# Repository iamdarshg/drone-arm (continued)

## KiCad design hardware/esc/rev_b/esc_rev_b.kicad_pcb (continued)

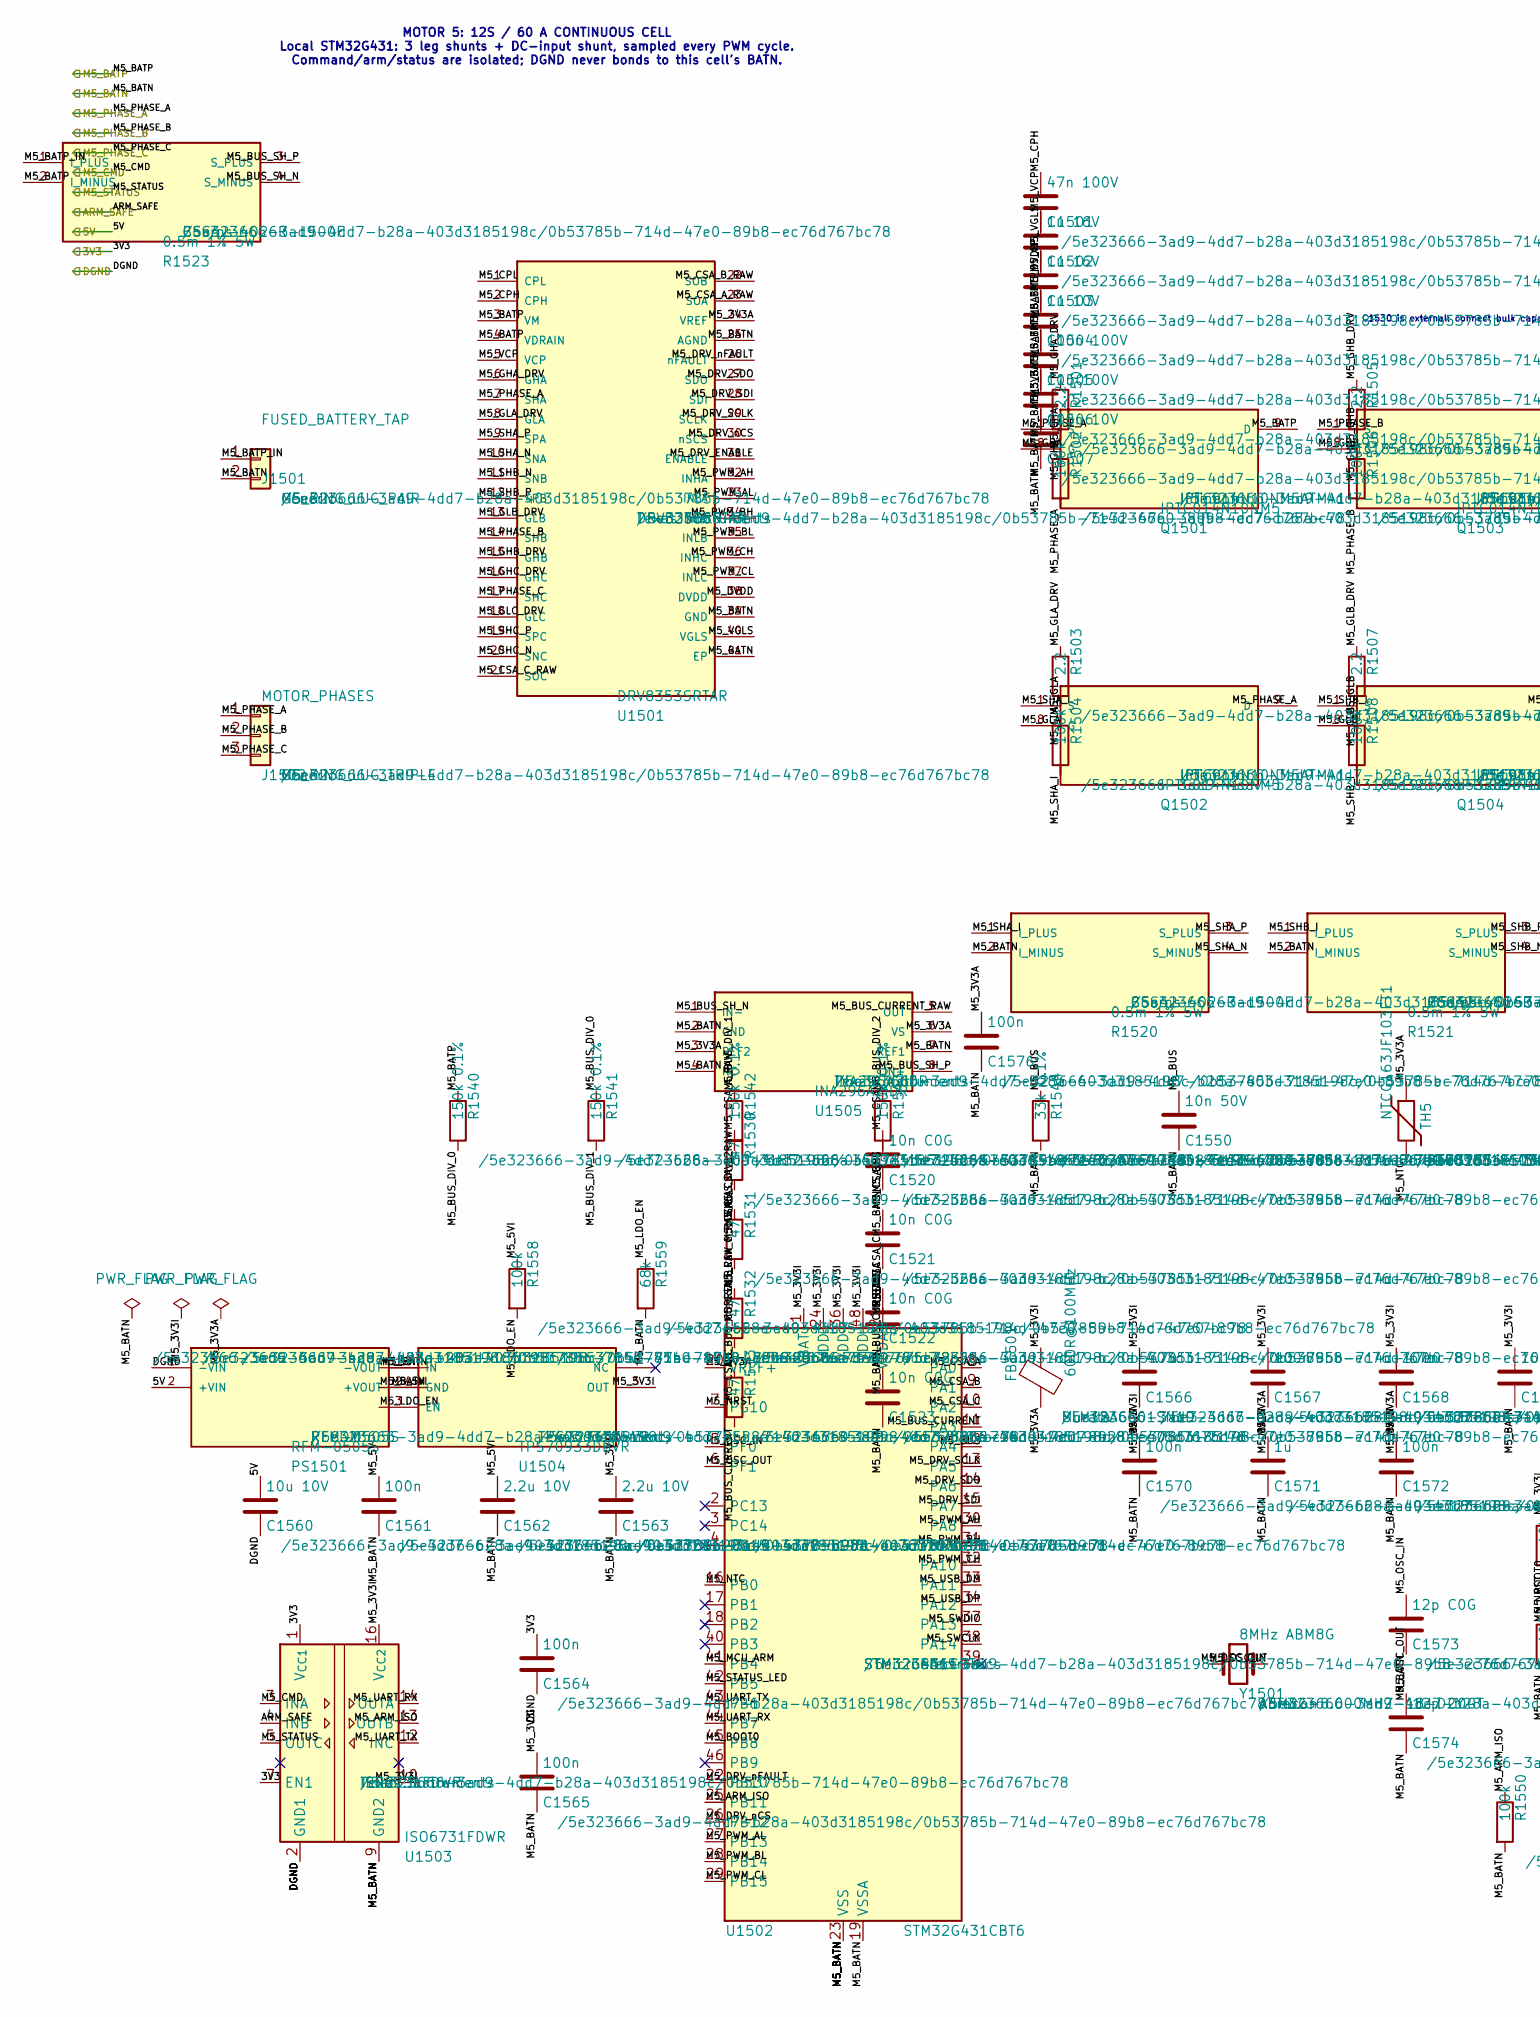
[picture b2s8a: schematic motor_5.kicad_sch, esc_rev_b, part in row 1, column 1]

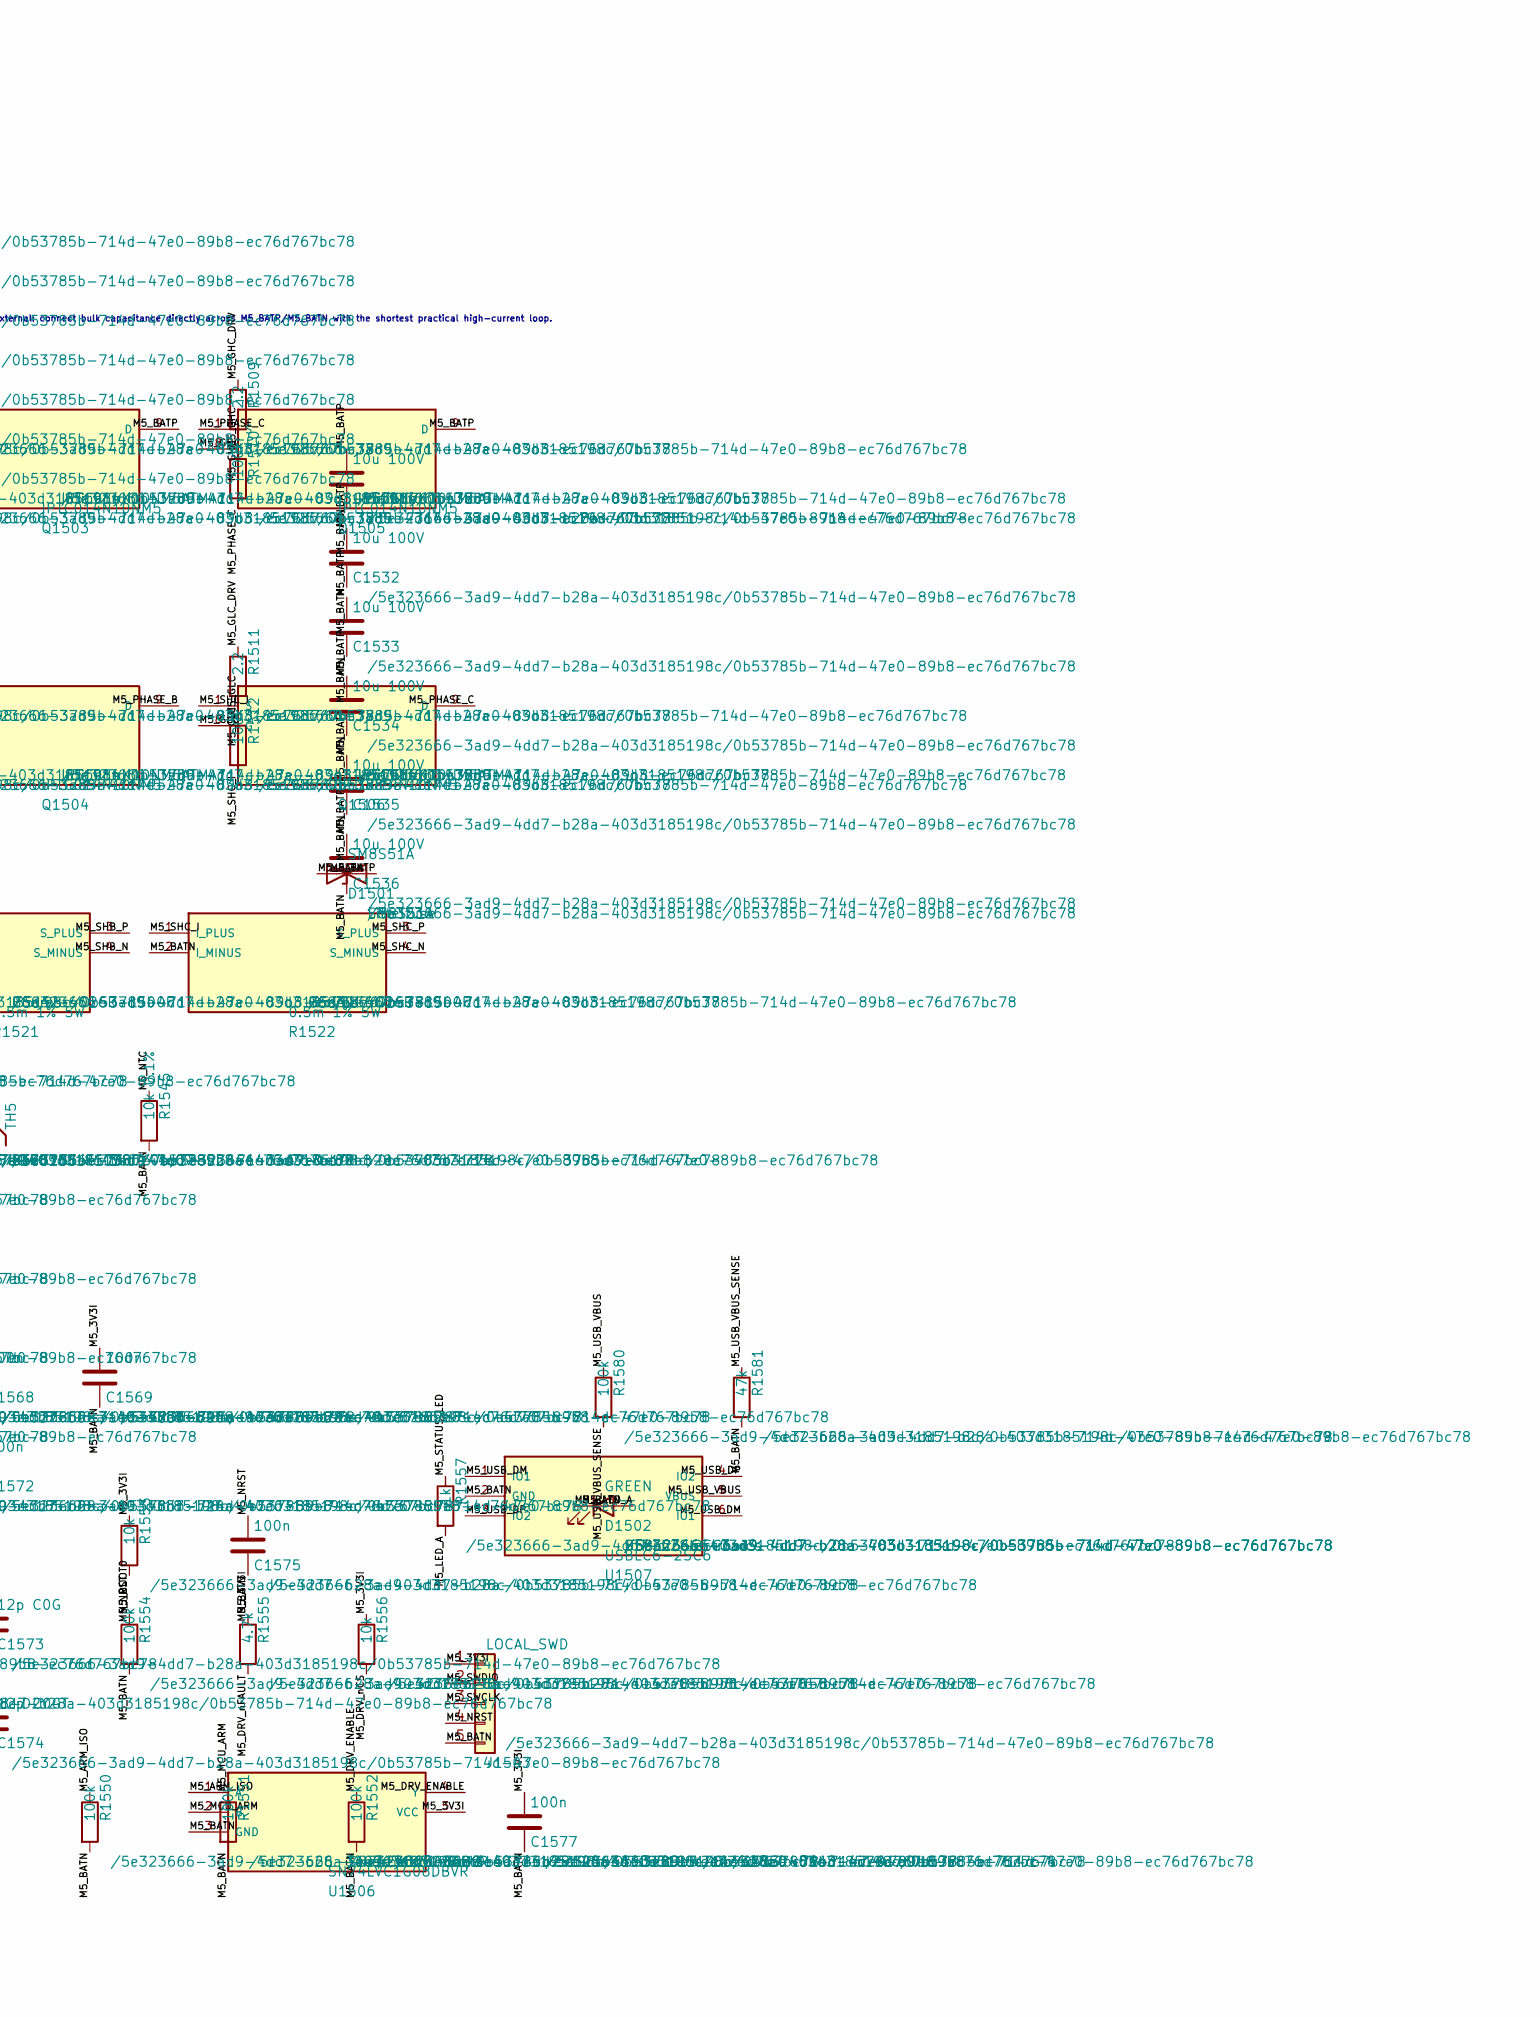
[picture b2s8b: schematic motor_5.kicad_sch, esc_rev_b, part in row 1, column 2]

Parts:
C1501: 47n 100V; C_0603_1608Metric
C1502, C1503: 1u 16V; C_0603_1608Metric
C1504: 1u 10V; C_0603_1608Metric
C1505: 100n 100V; C_0603_1608Metric
C1506, C1531, C1532, C1533, C1534, C1535, C1536: 10u 100V; C_1210_3225Metric
C1507: 100n 10V; C_0603_1608Metric
C1520, C1521, C1522, C1523: 10n C0G; C_0603_1608Metric
C1550: 10n 50V; C_0603_1608Metric
C1560: 10u 10V; C_0805_2012Metric
C1561, C1564, C1565, C1575, C1576, C1577: 100n; C_0603_1608Metric
C1562, C1563: 2.2u 10V; C_0603_1608Metric
C1566: 4.7u; C_0603_1608Metric
C1567, C1568, C1569, C1570, C1572: 100n; C_0402_1005Metric
C1571: 1u; C_0603_1608Metric
C1573, C1574: 12p C0G; C_0402_1005Metric
D1501: SM8S51A; DO-218AB_SM8S; MPN SM8S51A
D1502: GREEN; LED_0603_1608Metric
FB1501: 600R@100MHz; L_0603_1608Metric; MPN BLM18AG601SN1D
J1501: FUSED_BATTERY_TAP; POWER_LUG_M5_2P_P20; MPN M5_RING_LUG_PAIR
J1502: MOTOR_PHASES; POWER_LUG_M5_3P_P20; MPN M5_RING_LUG_TRIPLE
J1503: LOCAL_SWD; PinHeader_1x05_P1.27mm_Vertical
PS1501: RFM-0505S; RFM_SIP4_11.5x6_P2.54; MPN RFM-0505S
Q1501, Q1502, Q1503, Q1504, Q1505, Q1506: IPTC014N10NM5; PG-HDSOP-16_TOLT_IPTC; MPN IPTC014N10NM5ATMA1
R1501, R1503, R1505, R1507, R1509, R1511: 2.2; R_0603_1608Metric
R1502, R1504, R1506, R1508, R1510, R1512, R1550, R1551, R1552, R1554, R1558, R1580: 100k; R_0603_1608Metric
R1520, R1521, R1522, R1523: 0.5m 1% 5W; CSS4J-4026_Kelvin; MPN CSS4J-4026R-L500F
R1530, R1531, R1532, R1533: 47; R_0603_1608Metric
R1540, R1541, R1542, R1543: 150k 0.1%; R_1206_3216Metric
R1544: 33k 0.1%; R_0603_1608Metric
R1545: 10k 0.1%; R_0603_1608Metric
R1553, R1556: 10k; R_0603_1608Metric
R1555: 4.7k; R_0603_1608Metric
R1557: 1k; R_0603_1608Metric
R1559: 68k; R_0603_1608Metric
R1581: 47k; R_0603_1608Metric
TH5: NTCG163JF103FT1; R_0603_1608Metric; MPN NTCG163JF103FT1
U1501: DRV8353SRTAR; WQFN-40-EP_6x6_P0.5; MPN DRV8353SRTAR
U1502: STM32G431CBT6; LQFP-48_7x7mm_P0.5mm; MPN STM32G431CBT6
U1503: ISO6731FDWR; SOIC-16W_7.5x10.3mm_P1.27mm; MPN ISO6731FDWR
U1504: TPS70933DBVR; SOT-23-5; MPN TPS70933DBVR
U1505: INA296A2IDR; SOIC-8_3.9x4.9mm_P1.27mm; MPN INA296A2IDR
U1506: SN74LVC1G08DBVR; SOT-23-5; MPN SN74LVC1G08DBVR
U1507: USBLC6-2SC6; SOT-23-6; MPN USBLC6-2SC6
Y1501: 8MHz ABM8G; Crystal_SMD_3225-4Pin_3.2x2.5mm; MPN ABM8G-8.000MHZ-18-D2Y-T

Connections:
/3V3: C1564.1, U1503.1 (V_{CC1}), U1503.7 (EN1); also elsewhere on the board
/5V: C1560.1, PS1501.2 (+VIN); also elsewhere on the board
/ARM_SAFE: U1503.4 (INB); also elsewhere on the board
/DGND: C1560.2, C1564.2, PS1501.1 (-VIN), U1503.2 (GND1), U1503.8 (GND1); also elsewhere on the board
/M5_BATN: C1503.2, C1504.2, C1505.2, C1506.2, C1507.2, C1520.2, C1521.2, C1522.2, C1523.2, C1531.2, C1532.2, C1533.2, C1534.2, C1535.2, C1536.2, C1550.2, C1561.2, C1562.2, C1563.2, C1565.2, C1566.2, C1567.2, C1568.2, C1569.2, C1570.2, C1571.2, C1572.2, C1573.2, C1574.2, C1575.2, C1576.2, C1577.2, D1501.1 (A1), D1502.1 (K), J1501.2, J1503.5, PS1501.3 (-VOUT), R1520.2 (I_MINUS), R1521.2 (I_MINUS), R1522.2 (I_MINUS), R1544.2, R1545.2, R1550.2, R1551.2, R1552.2, R1554.2, R1559.2, R1581.2, U1501.25 (AGND), U1501.39 (GND), U1501.41 (EP), U1502.19 (VSSA), U1502.23 (VSS), U1502.35 (VSS), U1502.47 (VSS), U1503.9 (GND2), U1503.15 (GND2), U1504.2 (GND), U1505.2 (GND), U1505.4 (NC), U1505.7 (REF1), U1506.3 (GND), U1507.2 (GND); also elsewhere on the board
/M5_BATP: C1502.2, C1505.1, C1506.1, C1531.1, C1532.1, C1533.1, C1534.1, C1535.1, C1536.1, D1501.2 (A2), Q1501.9 (D), Q1503.9 (D), Q1505.9 (D), R1523.2 (I_MINUS), R1540.1, U1501.3 (VM), U1501.4 (VDRAIN); also elsewhere on the board
/M5_CMD: U1503.3 (INA); also elsewhere on the board
/M5_PHASE_A: J1502.1, Q1501.1 (S), Q1502.9 (D), R1502.2, U1501.7 (SHA)
/M5_PHASE_B: J1502.2, Q1503.1 (S), Q1504.9 (D), R1506.2, U1501.14 (SHB)
/M5_PHASE_C: J1502.3, Q1505.1 (S), Q1506.9 (D), R1510.2, U1501.17 (SHC)
/M5_STATUS: U1503.5 (OUTC); also elsewhere on the board
/Motor 5 power cell/M5_3V3A: C1507.1, C1571.1, C1572.1, C1576.1, FB1501.2, TH5.1, U1501.24 (VREF), U1502.20 (VREF+), U1502.21 (VDDA), U1505.3 (REF2), U1505.6 (VS)
/Motor 5 power cell/M5_3V3I: C1563.1, C1565.1, C1566.1, C1567.1, C1568.1, C1569.1, C1570.1, C1577.1, FB1501.1, J1503.1, R1553.1, R1555.1, R1556.1, U1502.1 (VBAT), U1502.24 (VDD), U1502.36 (VDD), U1502.48 (VDD), U1503.10 (EN2), U1503.16 (V_{CC2}), U1504.5 (OUT), U1506.5 (VCC)
/Motor 5 power cell/M5_5VI: C1561.1, C1562.1, PS1501.4 (+VOUT), R1558.1, U1504.1 (IN)
/Motor 5 power cell/M5_ARM_ISO: R1550.1, U1502.25 (PB11), U1503.13 (OUTB), U1506.1 (A)
/Motor 5 power cell/M5_BATP_IN: J1501.1, R1523.1 (I_PLUS)
/Motor 5 power cell/M5_BOOT0: R1554.1, U1502.45 (PB8)
/Motor 5 power cell/M5_BUS: C1550.1, R1543.2, R1544.1, U1502.12 (PA4)
/Motor 5 power cell/M5_BUS_CURRENT: C1523.1, R1533.2, U1502.11 (PA3)
/Motor 5 power cell/M5_BUS_CURRENT_RAW: R1533.1, U1505.5 (OUT)
/Motor 5 power cell/M5_BUS_DIV_0: R1540.2, R1541.1
/Motor 5 power cell/M5_BUS_DIV_1: R1541.2, R1542.1
/Motor 5 power cell/M5_BUS_DIV_2: R1542.2, R1543.1
/Motor 5 power cell/M5_BUS_SH_N: R1523.4 (S_MINUS), U1505.1 (IN-)
/Motor 5 power cell/M5_BUS_SH_P: R1523.3 (S_PLUS), U1505.8 (IN+)
/Motor 5 power cell/M5_CPH: C1501.1, U1501.2 (CPH)
/Motor 5 power cell/M5_CPL: C1501.2, U1501.1 (CPL)
/Motor 5 power cell/M5_CSA_A: C1520.1, R1530.2, U1502.8 (PA0)
/Motor 5 power cell/M5_CSA_A_RAW: R1530.1, U1501.23 (SOA)
/Motor 5 power cell/M5_CSA_B: C1521.1, R1531.2, U1502.9 (PA1)
/Motor 5 power cell/M5_CSA_B_RAW: R1531.1, U1501.22 (SOB)
/Motor 5 power cell/M5_CSA_C: C1522.1, R1532.2, U1502.10 (PA2)
/Motor 5 power cell/M5_CSA_C_RAW: R1532.1, U1501.21 (SOC)
/Motor 5 power cell/M5_DRV_ENABLE: R1552.1, U1501.31 (ENABLE), U1506.4 (Y)
/Motor 5 power cell/M5_DRV_SCLK: U1501.29 (SCLK), U1502.13 (PA5)
/Motor 5 power cell/M5_DRV_SDI: U1501.28 (SDI), U1502.15 (PA7)
/Motor 5 power cell/M5_DRV_SDO: U1501.27 (SDO), U1502.14 (PA6)
/Motor 5 power cell/M5_DRV_nCS: R1556.2, U1501.30 (nSCS), U1502.26 (PB12)
/Motor 5 power cell/M5_DRV_nFAULT: R1555.2, U1501.26 (nFAULT), U1502.22 (PB10)
/Motor 5 power cell/M5_DVDD: C1504.1, U1501.38 (DVDD)
/Motor 5 power cell/M5_GHA: Q1501.8 (G), R1501.2, R1502.1
/Motor 5 power cell/M5_GHA_DRV: R1501.1, U1501.6 (GHA)
/Motor 5 power cell/M5_GHB: Q1503.8 (G), R1505.2, R1506.1
/Motor 5 power cell/M5_GHB_DRV: R1505.1, U1501.15 (GHB)
/Motor 5 power cell/M5_GHC: Q1505.8 (G), R1509.2, R1510.1
/Motor 5 power cell/M5_GHC_DRV: R1509.1, U1501.16 (GHC)
/Motor 5 power cell/M5_GLA: Q1502.8 (G), R1503.2, R1504.1
/Motor 5 power cell/M5_GLA_DRV: R1503.1, U1501.8 (GLA)
/Motor 5 power cell/M5_GLB: Q1504.8 (G), R1507.2, R1508.1
/Motor 5 power cell/M5_GLB_DRV: R1507.1, U1501.13 (GLB)
/Motor 5 power cell/M5_GLC: Q1506.8 (G), R1511.2, R1512.1
/Motor 5 power cell/M5_GLC_DRV: R1511.1, U1501.18 (GLC)
/Motor 5 power cell/M5_LDO_EN: R1558.2, R1559.1, U1504.3 (EN)
/Motor 5 power cell/M5_LED_A: D1502.2 (A), R1557.2
/Motor 5 power cell/M5_MCU_ARM: R1551.1, U1502.41 (PB4), U1506.2 (B)
/Motor 5 power cell/M5_NRST: C1575.1, J1503.4, R1553.2, U1502.7 (PG10)
/Motor 5 power cell/M5_NTC: R1545.1, TH5.2, U1502.16 (PB0)
/Motor 5 power cell/M5_OSC_IN: C1573.1, U1502.5 (PF0), Y1501.1
/Motor 5 power cell/M5_OSC_OUT: C1574.1, U1502.6 (PF1), Y1501.2
/Motor 5 power cell/M5_PWM_AH: U1501.32 (INHA), U1502.30 (PA8)
/Motor 5 power cell/M5_PWM_AL: U1501.33 (INLA), U1502.27 (PB13)
/Motor 5 power cell/M5_PWM_BH: U1501.34 (INHB), U1502.31 (PA9)
/Motor 5 power cell/M5_PWM_BL: U1501.35 (INLB), U1502.28 (PB14)
/Motor 5 power cell/M5_PWM_CH: U1501.36 (INHC), U1502.32 (PA10)
/Motor 5 power cell/M5_PWM_CL: U1501.37 (INLC), U1502.29 (PB15)
/Motor 5 power cell/M5_SHA_I: Q1502.1 (S), R1504.2, R1520.1 (I_PLUS)
/Motor 5 power cell/M5_SHA_N: R1520.4 (S_MINUS), U1501.10 (SNA)
/Motor 5 power cell/M5_SHA_P: R1520.3 (S_PLUS), U1501.9 (SPA)
/Motor 5 power cell/M5_SHB_I: Q1504.1 (S), R1508.2, R1521.1 (I_PLUS)
/Motor 5 power cell/M5_SHB_N: R1521.4 (S_MINUS), U1501.11 (SNB)
/Motor 5 power cell/M5_SHB_P: R1521.3 (S_PLUS), U1501.12 (SPB)
/Motor 5 power cell/M5_SHC_I: Q1506.1 (S), R1512.2, R1522.1 (I_PLUS)
/Motor 5 power cell/M5_SHC_N: R1522.4 (S_MINUS), U1501.20 (SNC)
/Motor 5 power cell/M5_SHC_P: R1522.3 (S_PLUS), U1501.19 (SPC)
/Motor 5 power cell/M5_STATUS_LED: R1557.1, U1502.42 (PB5)
/Motor 5 power cell/M5_SWCLK: J1503.3, U1502.38 (PA14)
/Motor 5 power cell/M5_SWDIO: J1503.2, U1502.37 (PA13)
/Motor 5 power cell/M5_UART_RX: U1502.44 (PB7), U1503.14 (OUTA)
/Motor 5 power cell/M5_UART_TX: U1502.43 (PB6), U1503.12 (INC)
/Motor 5 power cell/M5_USB_DM: U1502.33 (PA11), U1507.1 (IO1), U1507.6 (IO1)
/Motor 5 power cell/M5_USB_DP: U1502.34 (PA12), U1507.3 (IO2), U1507.4 (IO2)
/Motor 5 power cell/M5_USB_VBUS: R1580.1, U1507.5 (VBUS)
/Motor 5 power cell/M5_USB_VBUS_SENSE: R1580.2, R1581.1
/Motor 5 power cell/M5_VCP: C1502.1, U1501.5 (VCP)
/Motor 5 power cell/M5_VGLS: C1503.1, U1501.40 (VGLS)

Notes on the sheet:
MOTOR 5: 12S / 60 A CONTINUOUS CELL Local STM32G431: 3 leg shunts + DC-input shunt, sampled every PWM cycle. Command/arm/status are isolated; DGND never bonds to this cell's BATN.
C1530 is external: connect bulk capacitance directly across M5_BATP/M5_BATN with the shortest practical high-current loop.

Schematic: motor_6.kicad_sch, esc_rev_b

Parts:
C1601: 47n 100V; C_0603_1608Metric
C1602, C1603: 1u 16V; C_0603_1608Metric
C1604: 1u 10V; C_0603_1608Metric
C1605: 100n 100V; C_0603_1608Metric
C1606, C1631, C1632, C1633, C1634, C1635, C1636: 10u 100V; C_1210_3225Metric
C1607: 100n 10V; C_0603_1608Metric
C1620, C1621, C1622, C1623: 10n C0G; C_0603_1608Metric
C1650: 10n 50V; C_0603_1608Metric
C1660: 10u 10V; C_0805_2012Metric
C1661, C1664, C1665, C1675, C1676, C1677: 100n; C_0603_1608Metric
C1662, C1663: 2.2u 10V; C_0603_1608Metric
C1666: 4.7u; C_0603_1608Metric
C1667, C1668, C1669, C1670, C1672: 100n; C_0402_1005Metric
C1671: 1u; C_0603_1608Metric
C1673, C1674: 12p C0G; C_0402_1005Metric
D1601: SM8S51A; DO-218AB_SM8S; MPN SM8S51A
D1602: GREEN; LED_0603_1608Metric
FB1601: 600R@100MHz; L_0603_1608Metric; MPN BLM18AG601SN1D
J1601: FUSED_BATTERY_TAP; POWER_LUG_M5_2P_P20; MPN M5_RING_LUG_PAIR
J1602: MOTOR_PHASES; POWER_LUG_M5_3P_P20; MPN M5_RING_LUG_TRIPLE
J1603: LOCAL_SWD; PinHeader_1x05_P1.27mm_Vertical
J1604: USB_DFU_SERVICE; JST_GH_SM06B-GHS-TB_1x06-1MP_P1.25mm_Horizontal; MPN SM06B-GHS-TB
PS1601: RFM-0505S; RFM_SIP4_11.5x6_P2.54; MPN RFM-0505S
Q1601, Q1602, Q1603, Q1604, Q1605, Q1606: IPTC014N10NM5; PG-HDSOP-16_TOLT_IPTC; MPN IPTC014N10NM5ATMA1
R1601, R1603, R1605, R1607, R1609, R1611: 2.2; R_0603_1608Metric
R1602, R1604, R1606, R1608, R1610, R1612, R1650, R1651, R1652, R1654, R1658, R1680: 100k; R_0603_1608Metric
R1620, R1621, R1622, R1623: 0.5m 1% 5W; CSS4J-4026_Kelvin; MPN CSS4J-4026R-L500F
R1630, R1631, R1632, R1633: 47; R_0603_1608Metric
R1640, R1641, R1642, R1643: 150k 0.1%; R_1206_3216Metric
R1644: 33k 0.1%; R_0603_1608Metric
R1645: 10k 0.1%; R_0603_1608Metric
R1653, R1656: 10k; R_0603_1608Metric
R1655: 4.7k; R_0603_1608Metric
R1657: 1k; R_0603_1608Metric
R1659: 68k; R_0603_1608Metric
R1681: 47k; R_0603_1608Metric
R1682, R1683, R1684: 0; R_0603_1608Metric
TH6: NTCG163JF103FT1; R_0603_1608Metric; MPN NTCG163JF103FT1
U1601: DRV8353SRTAR; WQFN-40-EP_6x6_P0.5; MPN DRV8353SRTAR
U1602: STM32G431CBT6; LQFP-48_7x7mm_P0.5mm; MPN STM32G431CBT6
U1603: ISO6731FDWR; SOIC-16W_7.5x10.3mm_P1.27mm; MPN ISO6731FDWR
U1604: TPS70933DBVR; SOT-23-5; MPN TPS70933DBVR
U1605: INA296A2IDR; SOIC-8_3.9x4.9mm_P1.27mm; MPN INA296A2IDR
U1606: SN74LVC1G08DBVR; SOT-23-5; MPN SN74LVC1G08DBVR
U1607: USBLC6-2SC6; SOT-23-6; MPN USBLC6-2SC6
Y1601: 8MHz ABM8G; Crystal_SMD_3225-4Pin_3.2x2.5mm; MPN ABM8G-8.000MHZ-18-D2Y-T

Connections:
/3V3: C1664.1, U1603.1 (V_{CC1}), U1603.7 (EN1); also elsewhere on the board
/5V: C1660.1, PS1601.2 (+VIN); also elsewhere on the board
/ARM_SAFE: U1603.4 (INB); also elsewhere on the board
/DGND: C1660.2, C1664.2, PS1601.1 (-VIN), U1603.2 (GND1), U1603.8 (GND1); also elsewhere on the board
/M6_BATN: C1603.2, C1604.2, C1605.2, C1606.2, C1607.2, C1620.2, C1621.2, C1622.2, C1623.2, C1631.2, C1632.2, C1633.2, C1634.2, C1635.2, C1636.2, C1650.2, C1661.2, C1662.2, C1663.2, C1665.2, C1666.2, C1667.2, C1668.2, C1669.2, C1670.2, C1671.2, C1672.2, C1673.2, C1674.2, C1675.2, C1676.2, C1677.2, D1601.1 (A1), D1602.1 (K), J1601.2, J1603.5, PS1601.3 (-VOUT), R1620.2 (I_MINUS), R1621.2 (I_MINUS), R1622.2 (I_MINUS), R1644.2, R1645.2, R1650.2, R1651.2, R1652.2, R1654.2, R1659.2, R1681.2, R1682.2, U1601.25 (AGND), U1601.39 (GND), U1601.41 (EP), U1602.19 (VSSA), U1602.23 (VSS), U1602.35 (VSS), U1602.47 (VSS), U1603.9 (GND2), U1603.15 (GND2), U1604.2 (GND), U1605.2 (GND), U1605.4 (NC), U1605.7 (REF1), U1606.3 (GND), U1607.2 (GND); also elsewhere on the board
/M6_BATP: C1602.2, C1605.1, C1606.1, C1631.1, C1632.1, C1633.1, C1634.1, C1635.1, C1636.1, D1601.2 (A2), Q1601.9 (D), Q1603.9 (D), Q1605.9 (D), R1623.2 (I_MINUS), R1640.1, U1601.3 (VM), U1601.4 (VDRAIN); also elsewhere on the board
/M6_CMD: U1603.3 (INA); also elsewhere on the board
/M6_PHASE_A: J1602.1, Q1601.1 (S), Q1602.9 (D), R1602.2, U1601.7 (SHA)
/M6_PHASE_B: J1602.2, Q1603.1 (S), Q1604.9 (D), R1606.2, U1601.14 (SHB)
/M6_PHASE_C: J1602.3, Q1605.1 (S), Q1606.9 (D), R1610.2, U1601.17 (SHC)
/M6_STATUS: U1603.5 (OUTC); also elsewhere on the board
/Motor 6 power cell/M6_3V3A: C1607.1, C1671.1, C1672.1, C1676.1, FB1601.2, TH6.1, U1601.24 (VREF), U1602.20 (VREF+), U1602.21 (VDDA), U1605.3 (REF2), U1605.6 (VS)
/Motor 6 power cell/M6_3V3I: C1663.1, C1665.1, C1666.1, C1667.1, C1668.1, C1669.1, C1670.1, C1677.1, FB1601.1, J1603.1, R1653.1, R1655.1, R1656.1, U1602.1 (VBAT), U1602.24 (VDD), U1602.36 (VDD), U1602.48 (VDD), U1603.10 (EN2), U1603.16 (V_{CC2}), U1604.5 (OUT), U1606.5 (VCC)
/Motor 6 power cell/M6_5VI: C1661.1, C1662.1, PS1601.4 (+VOUT), R1658.1, U1604.1 (IN)
/Motor 6 power cell/M6_ARM_ISO: R1650.1, U1602.25 (PB11), U1603.13 (OUTB), U1606.1 (A)
/Motor 6 power cell/M6_BATP_IN: J1601.1, R1623.1 (I_PLUS)
/Motor 6 power cell/M6_BOOT0: R1654.1, R1683.2, U1602.45 (PB8)
/Motor 6 power cell/M6_BUS: C1650.1, R1643.2, R1644.1, U1602.12 (PA4)
/Motor 6 power cell/M6_BUS_CURRENT: C1623.1, R1633.2, U1602.11 (PA3)
/Motor 6 power cell/M6_BUS_CURRENT_RAW: R1633.1, U1605.5 (OUT)
/Motor 6 power cell/M6_BUS_DIV_0: R1640.2, R1641.1
/Motor 6 power cell/M6_BUS_DIV_1: R1641.2, R1642.1
/Motor 6 power cell/M6_BUS_DIV_2: R1642.2, R1643.1
/Motor 6 power cell/M6_BUS_SH_N: R1623.4 (S_MINUS), U1605.1 (IN-)
/Motor 6 power cell/M6_BUS_SH_P: R1623.3 (S_PLUS), U1605.8 (IN+)
/Motor 6 power cell/M6_CPH: C1601.1, U1601.2 (CPH)
/Motor 6 power cell/M6_CPL: C1601.2, U1601.1 (CPL)
/Motor 6 power cell/M6_CSA_A: C1620.1, R1630.2, U1602.8 (PA0)
/Motor 6 power cell/M6_CSA_A_RAW: R1630.1, U1601.23 (SOA)
/Motor 6 power cell/M6_CSA_B: C1621.1, R1631.2, U1602.9 (PA1)
/Motor 6 power cell/M6_CSA_B_RAW: R1631.1, U1601.22 (SOB)
/Motor 6 power cell/M6_CSA_C: C1622.1, R1632.2, U1602.10 (PA2)
/Motor 6 power cell/M6_CSA_C_RAW: R1632.1, U1601.21 (SOC)
/Motor 6 power cell/M6_DRV_ENABLE: R1652.1, U1601.31 (ENABLE), U1606.4 (Y)
/Motor 6 power cell/M6_DRV_SCLK: U1601.29 (SCLK), U1602.13 (PA5)
/Motor 6 power cell/M6_DRV_SDI: U1601.28 (SDI), U1602.15 (PA7)
/Motor 6 power cell/M6_DRV_SDO: U1601.27 (SDO), U1602.14 (PA6)
/Motor 6 power cell/M6_DRV_nCS: R1656.2, U1601.30 (nSCS), U1602.26 (PB12)
/Motor 6 power cell/M6_DRV_nFAULT: R1655.2, U1601.26 (nFAULT), U1602.22 (PB10)
/Motor 6 power cell/M6_DVDD: C1604.1, U1601.38 (DVDD)
/Motor 6 power cell/M6_GHA: Q1601.8 (G), R1601.2, R1602.1
/Motor 6 power cell/M6_GHA_DRV: R1601.1, U1601.6 (GHA)
/Motor 6 power cell/M6_GHB: Q1603.8 (G), R1605.2, R1606.1
/Motor 6 power cell/M6_GHB_DRV: R1605.1, U1601.15 (GHB)
/Motor 6 power cell/M6_GHC: Q1605.8 (G), R1609.2, R1610.1
/Motor 6 power cell/M6_GHC_DRV: R1609.1, U1601.16 (GHC)
/Motor 6 power cell/M6_GLA: Q1602.8 (G), R1603.2, R1604.1
/Motor 6 power cell/M6_GLA_DRV: R1603.1, U1601.8 (GLA)
/Motor 6 power cell/M6_GLB: Q1604.8 (G), R1607.2, R1608.1
/Motor 6 power cell/M6_GLB_DRV: R1607.1, U1601.13 (GLB)
/Motor 6 power cell/M6_GLC: Q1606.8 (G), R1611.2, R1612.1
/Motor 6 power cell/M6_GLC_DRV: R1611.1, U1601.18 (GLC)
/Motor 6 power cell/M6_LDO_EN: R1658.2, R1659.1, U1604.3 (EN)
/Motor 6 power cell/M6_LED_A: D1602.2 (A), R1657.2
/Motor 6 power cell/M6_MCU_ARM: R1651.1, U1602.41 (PB4), U1606.2 (B)
/Motor 6 power cell/M6_NRST: C1675.1, J1603.4, R1653.2, R1684.2, U1602.7 (PG10)
/Motor 6 power cell/M6_NTC: R1645.1, TH6.2, U1602.16 (PB0)
/Motor 6 power cell/M6_OSC_IN: C1673.1, U1602.5 (PF0), Y1601.1
/Motor 6 power cell/M6_OSC_OUT: C1674.1, U1602.6 (PF1), Y1601.2
/Motor 6 power cell/M6_PWM_AH: U1601.32 (INHA), U1602.30 (PA8)
/Motor 6 power cell/M6_PWM_AL: U1601.33 (INLA), U1602.27 (PB13)
/Motor 6 power cell/M6_PWM_BH: U1601.34 (INHB), U1602.31 (PA9)
/Motor 6 power cell/M6_PWM_BL: U1601.35 (INLB), U1602.28 (PB14)
/Motor 6 power cell/M6_PWM_CH: U1601.36 (INHC), U1602.32 (PA10)
/Motor 6 power cell/M6_PWM_CL: U1601.37 (INLC), U1602.29 (PB15)
/Motor 6 power cell/M6_SHA_I: Q1602.1 (S), R1604.2, R1620.1 (I_PLUS)
/Motor 6 power cell/M6_SHA_N: R1620.4 (S_MINUS), U1601.10 (SNA)
/Motor 6 power cell/M6_SHA_P: R1620.3 (S_PLUS), U1601.9 (SPA)
/Motor 6 power cell/M6_SHB_I: Q1604.1 (S), R1608.2, R1621.1 (I_PLUS)
/Motor 6 power cell/M6_SHB_N: R1621.4 (S_MINUS), U1601.11 (SNB)
/Motor 6 power cell/M6_SHB_P: R1621.3 (S_PLUS), U1601.12 (SPB)
/Motor 6 power cell/M6_SHC_I: Q1606.1 (S), R1612.2, R1622.1 (I_PLUS)
/Motor 6 power cell/M6_SHC_N: R1622.4 (S_MINUS), U1601.20 (SNC)
/Motor 6 power cell/M6_SHC_P: R1622.3 (S_PLUS), U1601.19 (SPC)
/Motor 6 power cell/M6_STATUS_LED: R1657.1, U1602.42 (PB5)
/Motor 6 power cell/M6_SWCLK: J1603.3, U1602.38 (PA14)
/Motor 6 power cell/M6_SWDIO: J1603.2, U1602.37 (PA13)
/Motor 6 power cell/M6_UART_RX: U1602.44 (PB7), U1603.14 (OUTA)
/Motor 6 power cell/M6_UART_TX: U1602.43 (PB6), U1603.12 (INC)
/Motor 6 power cell/M6_USB_DM: J1604.2, U1602.33 (PA11), U1607.1 (IO1), U1607.6 (IO1)
/Motor 6 power cell/M6_USB_DP: J1604.1, U1602.34 (PA12), U1607.3 (IO2), U1607.4 (IO2)
/Motor 6 power cell/M6_USB_VBUS: J1604.4, R1680.1, U1607.5 (VBUS)
/Motor 6 power cell/M6_USB_VBUS_SENSE: R1680.2, R1681.1
/Motor 6 power cell/M6_VCP: C1602.1, U1601.5 (VCP)
/Motor 6 power cell/M6_VGLS: C1603.1, U1601.40 (VGLS)
unnamed: J1604.3, R1682.1
unnamed: J1604.5, R1683.1
unnamed: J1604.6, R1684.1

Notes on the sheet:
MOTOR 6: 12S / 60 A CONTINUOUS CELL Local STM32G431: 3 leg shunts + DC-input shunt, sampled every PWM cycle. Command/arm/status are isolated; DGND never bonds to this cell's BATN.
C1630 is external: connect bulk capacitance directly across M6_BATP/M6_BATN with the shortest practical high-current loop.

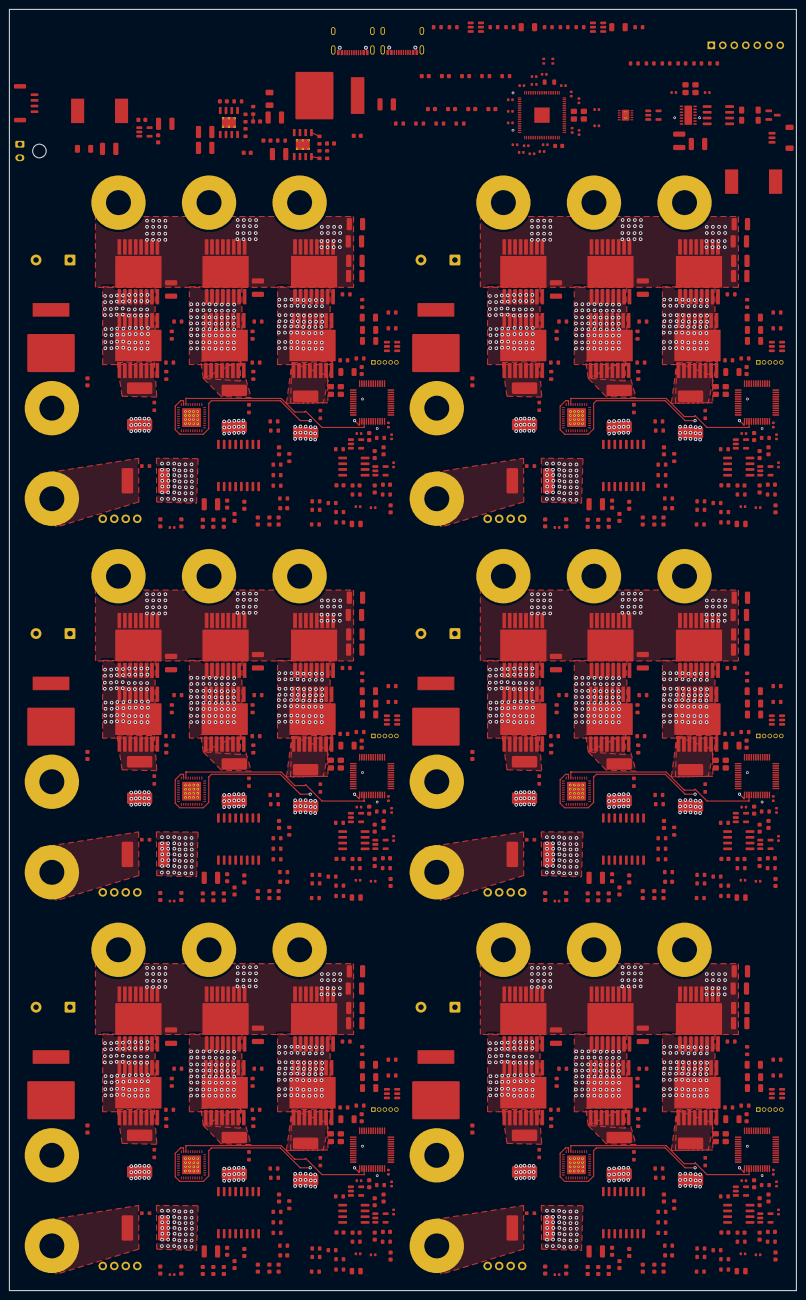
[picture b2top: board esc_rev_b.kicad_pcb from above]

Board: 4 copper layers, 173.8 x 282.9 mm, 687 parts (0 on the bottom side), 556 nets.

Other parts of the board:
C234, C235: 1n 2kV; C_1206_3216Metric
C1130, C1230, C1330, C1430, C1530, C1630: 820u 100V; CP_Radial_D18.0mm_P7.50mm
J202: CTRL_USB_C; USB_C_Receptacle_GCT_USB4105-xx-A_16P_TopMnt_Horizontal
J203: MOTOR_DFU_USB_C; USB_C_Receptacle_GCT_USB4105-xx-A_16P_TopMnt_Horizontal
R204, R205, R211, R212: 5.1k; R_0603_1608Metric
R206, R207: 27; R_0402_1005Metric
R208: 100k; R_0603_1608Metric
R209: 47k; R_0603_1608Metric
R210, R213: 1M; R_0603_1608Metric
R214, R215, R216, R217, R218, R219: 10k; R_0603_1608Metric
SW201: 6-WAY ACTIVE-LOW SELECTOR; PinHeader_1x07_P2.54mm_Vertical
U208, U209: USBLC6-2SC6; SOT-23-6

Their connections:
/3V3: R214.1, R215.1, R216.1, R217.1, R218.1, R219.1; also elsewhere on the board
/Controller and ADC/CTRL_USB_CC1: J202.A5, R204.1
/Controller and ADC/CTRL_USB_CC2: J202.B5, R205.1
/Controller and ADC/CTRL_USB_DM: R206.1, U208.6
/Controller and ADC/CTRL_USB_DM_CONN: J202.A7, J202.B7, U208.1
/Controller and ADC/CTRL_USB_DM_MCU: R206.2; also elsewhere on the board
/Controller and ADC/CTRL_USB_DP: R207.1, U208.4
/Controller and ADC/CTRL_USB_DP_CONN: J202.A6, J202.B6, U208.3
/Controller and ADC/CTRL_USB_DP_MCU: R207.2; also elsewhere on the board
/Controller and ADC/CTRL_USB_SHIELD: C234.1, J202.S1, R210.1
/Controller and ADC/CTRL_USB_VBUS: J202.A4, J202.A9, J202.B4, J202.B9, R208.1, U208.5
/Controller and ADC/CTRL_USB_VBUS_SENSE: R208.2, R209.1; also elsewhere on the board
/Controller and ADC/SVC_CELL1_SEL_N: R214.2, SW201.2
/Controller and ADC/SVC_CELL2_SEL_N: R215.2, SW201.3
/Controller and ADC/SVC_CELL3_SEL_N: R216.2, SW201.4
/Controller and ADC/SVC_CELL4_SEL_N: R217.2, SW201.5
/Controller and ADC/SVC_CELL5_SEL_N: R218.2, SW201.6
/Controller and ADC/SVC_CELL6_SEL_N: R219.2, SW201.7
/Controller and ADC/SVC_USB_CC1: J203.A5, R211.1
/Controller and ADC/SVC_USB_CC2: J203.B5, R212.1
/Controller and ADC/SVC_USB_DM_CONN: J203.A7, J203.B7, U209.1, U209.6
/Controller and ADC/SVC_USB_DP_CONN: J203.A6, J203.B6, U209.3, U209.4
/Controller and ADC/SVC_USB_GND: C235.2, J203.A1, J203.A12, J203.B1, J203.B12, R211.2, R212.2, R213.2, U209.2
/Controller and ADC/SVC_USB_SHIELD: C235.1, J203.S1, R213.1
/Controller and ADC/SVC_USB_VBUS: J203.A4, J203.A9, J203.B4, J203.B9, U209.5
/DGND: C234.2, J202.A1, J202.A12, J202.B1, J202.B12, R204.2, R205.2, R209.2, R210.2, SW201.1, U208.2; also elsewhere on the board
/M1_BATN: C1130.2; also elsewhere on the board
/M1_BATP: C1130.1; also elsewhere on the board
/M2_BATN: C1230.2; also elsewhere on the board
/M2_BATP: C1230.1; also elsewhere on the board
/M3_BATN: C1330.2; also elsewhere on the board
/M3_BATP: C1330.1; also elsewhere on the board
/M4_BATN: C1430.2; also elsewhere on the board
/M4_BATP: C1430.1; also elsewhere on the board
/M5_BATN: C1530.2; also elsewhere on the board
/M5_BATP: C1530.1; also elsewhere on the board
/M6_BATN: C1630.2; also elsewhere on the board
/M6_BATP: C1630.1; also elsewhere on the board
